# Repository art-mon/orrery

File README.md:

# About

This open-source project gathers small signals from the world and turns them into daily broadcasts of art, language, and atmosphere.

Using public data, curated artwork, short written messages, and generative AI, it tries to shape something clear and gentle—something that can inform, but also quietly accompany a moment in the day. The art is curated by friends and family, so the project grows not only from data, but also from taste, memory, and shared sensibility.

The goal is to keep each broadcast simple, beautiful, and easy to receive: a small composition made from information, care, and imagination.

Link to the preview:
https://art-mon.github.io/orrery/display/

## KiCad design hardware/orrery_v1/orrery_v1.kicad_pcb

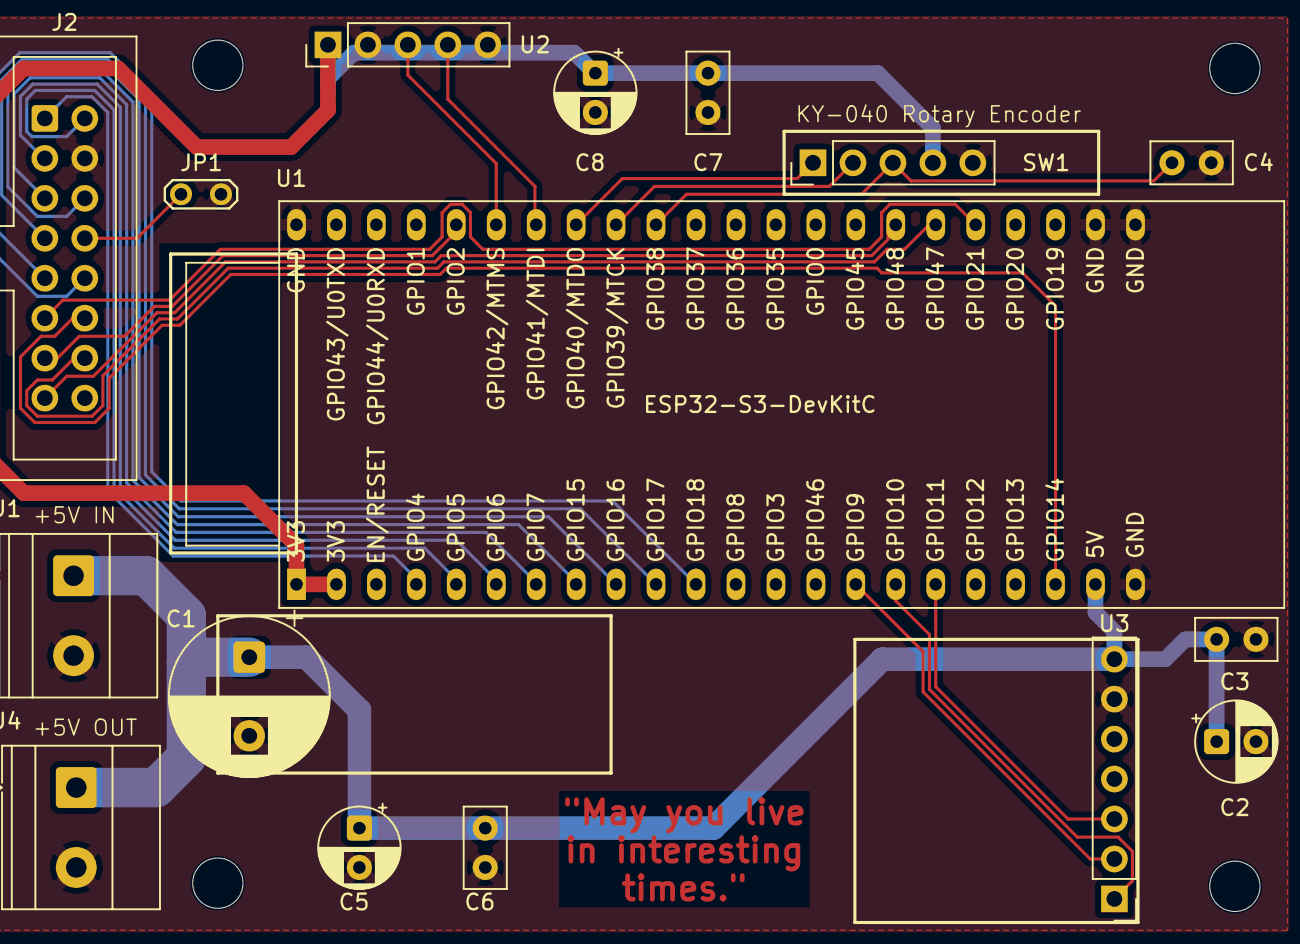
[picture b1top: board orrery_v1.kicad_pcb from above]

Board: 2 copper layers, 20 parts (0 on the bottom side), 25 nets.

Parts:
C1: 1000uF, 25V; CP_Radial_D10.0mm_P5.00mm
C2, C5, C8: 100uF, 25V; CP_Radial_D5.0mm_P2.50mm
C3, C4, C6, C7: 100nF, 100V; C_Disc_D5.0mm_W2.5mm_P2.50mm
H1, H2, H3, H4: MountingHole; MountingHole_3.2mm_M3_ISO7380
J1, J4: Screw_Terminal_01x02; TerminalBlock_Phoenix_MKDS-1,5-2-5.08_1x02_P5.08mm_Horizont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
J2: Conn_02x08_Odd_Even; IDC-Header_2x08_P2.54mm_Vertical
JP1: Jumper_2_Bridged; TestPoint_2Pads_Pitch2.54mm_Drill0.8mm
SW1: KY-040; PinHeader_1x05_P2.54mm_Vertical
U1: ESP32-S3-DevKitC
U2: BH1750_GY-302; PinHeader_1x05_P2.54mm_Vertical
U3: MAX98357A; PinHeader_1x07_P2.54mm_Vertical

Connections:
+3V3: C7.1, C8.1, SW1.4 (+), U1.1 (3V3), U1.2 (3V3), U2.1 (VCC)
+5V: C1.1, C2.1, C3.1, C5.1, C6.1, J1.1, J4.1, U1.21 (5V), U3.7 (VIN)
/BH1750_SCL: U1.39 (GPIO42/MTMS), U2.3 (SCL)
/BH1750_SDA: U1.38 (GPIO41/MTDI), U2.4 (SDA)
/HUB75_A: J2.9, U1.10 (GPIO17/ADC2_CH6)
/HUB75_B: J2.10, U1.11 (GPIO18/ADC2_CH7)
/HUB75_B1: J2.3, U1.6 (GPIO6/ADC1_CH5)
/HUB75_B2: J2.7, U1.9 (GPIO16/ADC2_CH5/32K_N)
/HUB75_C: J2.11, U1.27 (GPIO21)
/HUB75_CLK: J2.13, U1.40 (GPIO2/ADC1_CH1)
/HUB75_D: J2.12, U1.20 (GPIO14/ADC2_CH3)
/HUB75_G1: J2.2, U1.5 (GPIO5/ADC1_CH4)
/HUB75_G2: J2.6, U1.8 (GPIO15/ADC2_CH4/32K_P)
/HUB75_LAT: J2.14, U1.28 (GPIO47)
/HUB75_OE: J2.15, U1.29 (GPIO48)
/HUB75_R1: J2.1, U1.4 (GPIO4/ADC1_CH3)
/HUB75_R2: J2.5, U1.7 (GPIO7/ADC1_CH6)
/KY-040_CLK: SW1.1 (CLK), U1.37 (GPIO40/MTDO)
/KY-040_DT: SW1.2 (DT), U1.36 (GPIO39/MTCK)
/KY-040_SW: C4.1, SW1.3 (SW), U1.35 (GPIO38)
/MAX98357A_BCLK: U1.15 (GPIO9/ADC1_CH8), U3.2 (BCLK)
/MAX98357A_DIN: U1.17 (GPIO11/ADC2_CH0), U3.3 (DIN)
/MAX98357A_LRC: U1.16 (GPIO10/ADC1_CH9), U3.1 (LRC)
GND: C1.2, C2.2, C3.2, C4.2, C5.2, C6.2, C7.2, C8.2, J1.2, J2.4, J2.16, J4.2, JP1.2 (B), SW1.5 (GND), U1.22 (GND), U1.23 (GND), U1.24 (GND), U1.44 (GND), U2.2 (GND), U2.5 (ADDR), U3.6 (GND)
unnamed: J2.8, JP1.1 (A)
